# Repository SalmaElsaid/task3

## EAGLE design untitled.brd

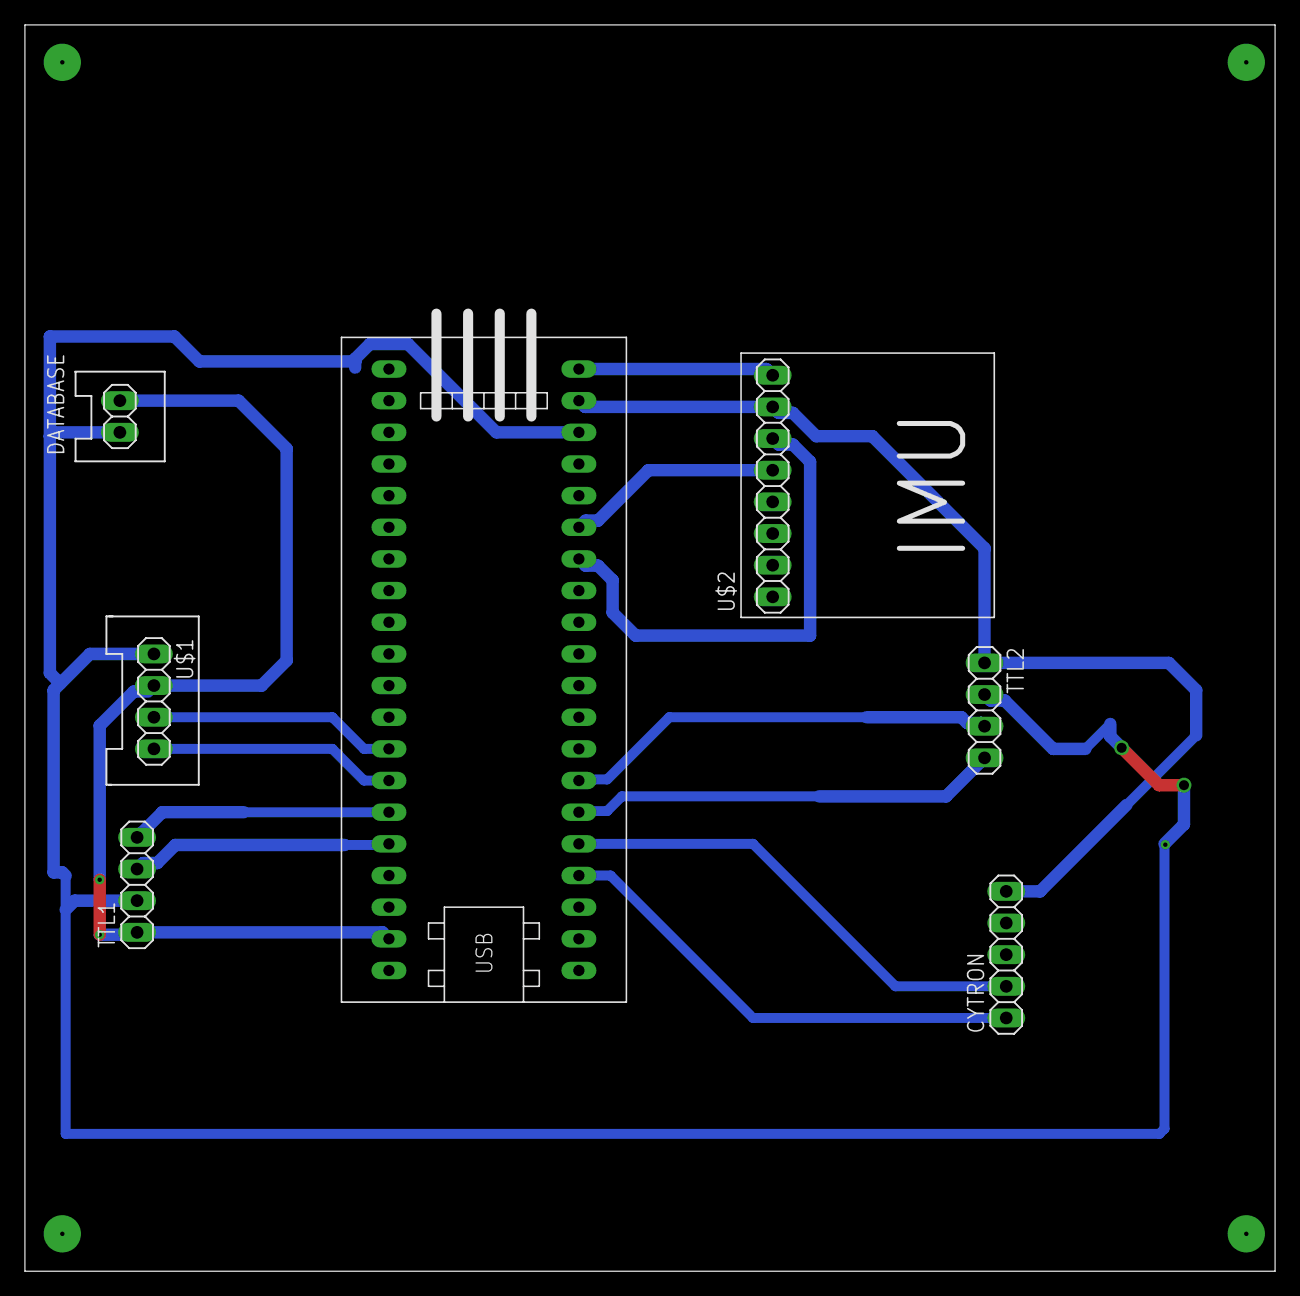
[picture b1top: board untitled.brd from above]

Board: 2 copper layers, 100.3 x 100.0 mm, 7 parts (0 on the bottom side), 14 nets.

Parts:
CYTRON: 1X05
DATABASE: 1X02_DATA
TTL1, TTL2: 1X04
U$1: ENCODER; 1X04_DATA
U$2: IMU_ROBOCON_GY521; IMU_GY521
U$3: STM32F103C8T6-MODULE

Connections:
3.3V1: U$2.VCC, U$3.3.3V_1
5V: DATABASE.2, TTL1.2, TTL2.2, U$1.1, U$3.5V
GND: CYTRON.5, TTL2.1, U$2.GND, U$3.GND_1
GND_1: DATABASE.1, TTL1.1, U$1.2, U$3.GND_2
PA_8: CYTRON.2, U$3.PA_8
PA_9: TTL2.4, U$3.PA_9
PA_10: TTL2.3, U$3.PA_10
PB_0: U$1.3, U$3.PB_0
PB_1: U$1.4, U$3.PB_1
PB_6: U$2.SCL, U$3.PB_6
PB_7: U$2.SDA, U$3.PB_7
PB_10: TTL1.4, U$3.PB_10
PB_11: TTL1.3, U$3.PB_11
PB_15: CYTRON.1, U$3.PB_15

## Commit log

2021-10-29 Create 1
